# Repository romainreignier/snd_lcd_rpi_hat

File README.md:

# snd_lcd_rpi_hat

Simple Raspberry Pi HAT PCB to plug a small TFT 2.4" LCD screen.

Designed for the Supmeca Never Dies (SND) team for Eurobot 2018.

The Kicad template is base on <https://github.com/xesscorp/RPi_Hat_Template>.

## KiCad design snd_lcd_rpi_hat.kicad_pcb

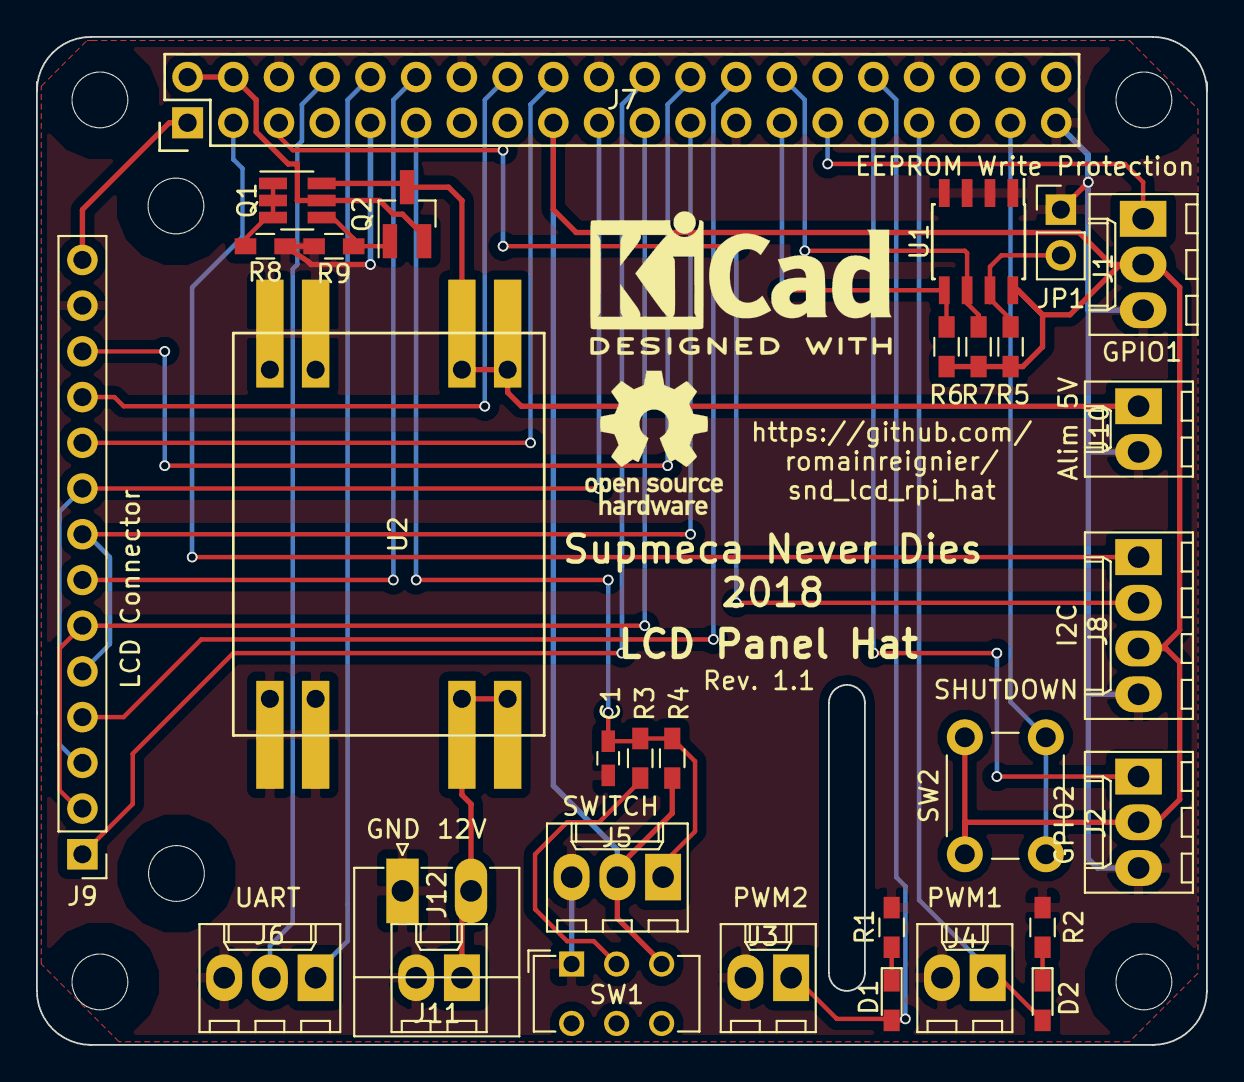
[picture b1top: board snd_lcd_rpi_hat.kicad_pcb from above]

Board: 2 copper layers, 65.0 x 56.0 mm, 31 parts (0 on the bottom side), 32 nets.

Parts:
C1: 0.1uF; C_0603_HandSoldering
D1, D2: LED; LED_0603_HandSoldering
J1, J2, J5, J6: Conn_01x03; Molex_KK-6410-03_03x2.54mm_Straight
J3, J4, J10, J11: Conn_01x02; Molex_KK-6410-02_02x2.54mm_Straight
J7: RPi_GPIO; Pin_Header_Straight_2x20
J8: Conn_01x04; Molex_KK-6410-04_04x2.54mm_Straight
J9: Conn_01x14; Pin_Header_Straight_1x14_Pitch2.54mm
J12: Conn_01x02; PhoenixContact_MC-G_02x3.81mm_Angled
JP1: Jumper; Pin_Header_Straight_1x02_Pitch2.54mm
Q1: DMMT5401; SOT-23-6_Handsoldering
Q2: DMG2305UX; SOT-23_Handsoldering
R1, R2: 330; R_0603_HandSoldering
R3, R5: 1k; R_0603_HandSoldering
R4, R8: 10k; R_0603_HandSoldering
R6, R7: 3.9k; R_0603_HandSoldering
R9: 47k; R_0603_HandSoldering
SW1: SW_DPDT_x2; SW_CuK_JS202011CQN_DPDT_Straight
SW2: SW_Push; SW_PUSH_6mm_h5mm
U1: AT24CS32-SSHM; SOIC-8_3.9x4.9mm_Pitch1.27mm
U2: DCDC-Converter_D-SUN; D-SUN

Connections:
+3V3: J1.2, J2.2, J5.2, J7.1, J7.17, J8.3, J9.14, R4.1, R5.1, R6.1, R7.1, SW1.3, SW2.1, U1.8
+12V: J11.1, J12.2, U2.2, U2.6
/EEPROM_SCL: J7.28, R7.2, U1.6
/EEPROM_SDA: J7.27, R6.2, U1.5
/GPIO1: J1.1, J7.29
/GPIO2: J2.1, J7.31
/I2C_SCL: J7.5, J8.2
/I2C_SDA: J7.3, J8.1
/LCD_CS: J7.24, J9.12
/LCD_DC: J7.18, J9.10
/LCD_LED: J7.12, J9.7
/LCD_MISO: J7.21, J9.2, J9.6
/LCD_MOSI: J7.19, J9.3, J9.9
/LCD_RESET: J7.16, J9.11
/LCD_SCLK: J7.23, J9.5, J9.8
/LED1: D1.2, J3.1, J7.32
/LED2: D2.2, J4.1, J7.33
/P5V_HAT: J7.2, J7.4, Q1.5, Q2.2
/P5V_POWER: J10.1, Q1.6, Q2.3, U2.3, U2.7
/SHUTDOWN: J7.37, SW2.2
/SWITCH: C1.1, J5.1, J7.11, R3.2, R4.2
/TOUCH_CS: J7.26, J9.4
/TOUCH_IRQ: J7.22, J9.1
/UART_RX: J6.1, J7.10
/UART_TX: J6.2, J7.8
GND: C1.2, J1.3, J2.3, J3.2, J4.2, J5.3, J6.3, J7.6, J7.9, J7.14, J7.20, J7.25, J7.34, J7.39, J8.4, J9.13, J10.2, J11.2, J12.1, JP1.1, R1.1, R2.1, R8.2, R9.2, SW1.1, U1.1, U1.2, U1.3, U1.4, U2.1, U2.4, U2.5, U2.8
unnamed: D1.1, R1.2
unnamed: D2.1, R2.2
unnamed: JP1.2, R5.2, U1.7
unnamed: Q1.1, Q1.2, Q1.3, R8.1
unnamed: Q1.4, Q2.1, R9.1
unnamed: R3.1, SW1.2

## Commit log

2018-03-23 Add missing track between Raspberry Pi header and the switch
